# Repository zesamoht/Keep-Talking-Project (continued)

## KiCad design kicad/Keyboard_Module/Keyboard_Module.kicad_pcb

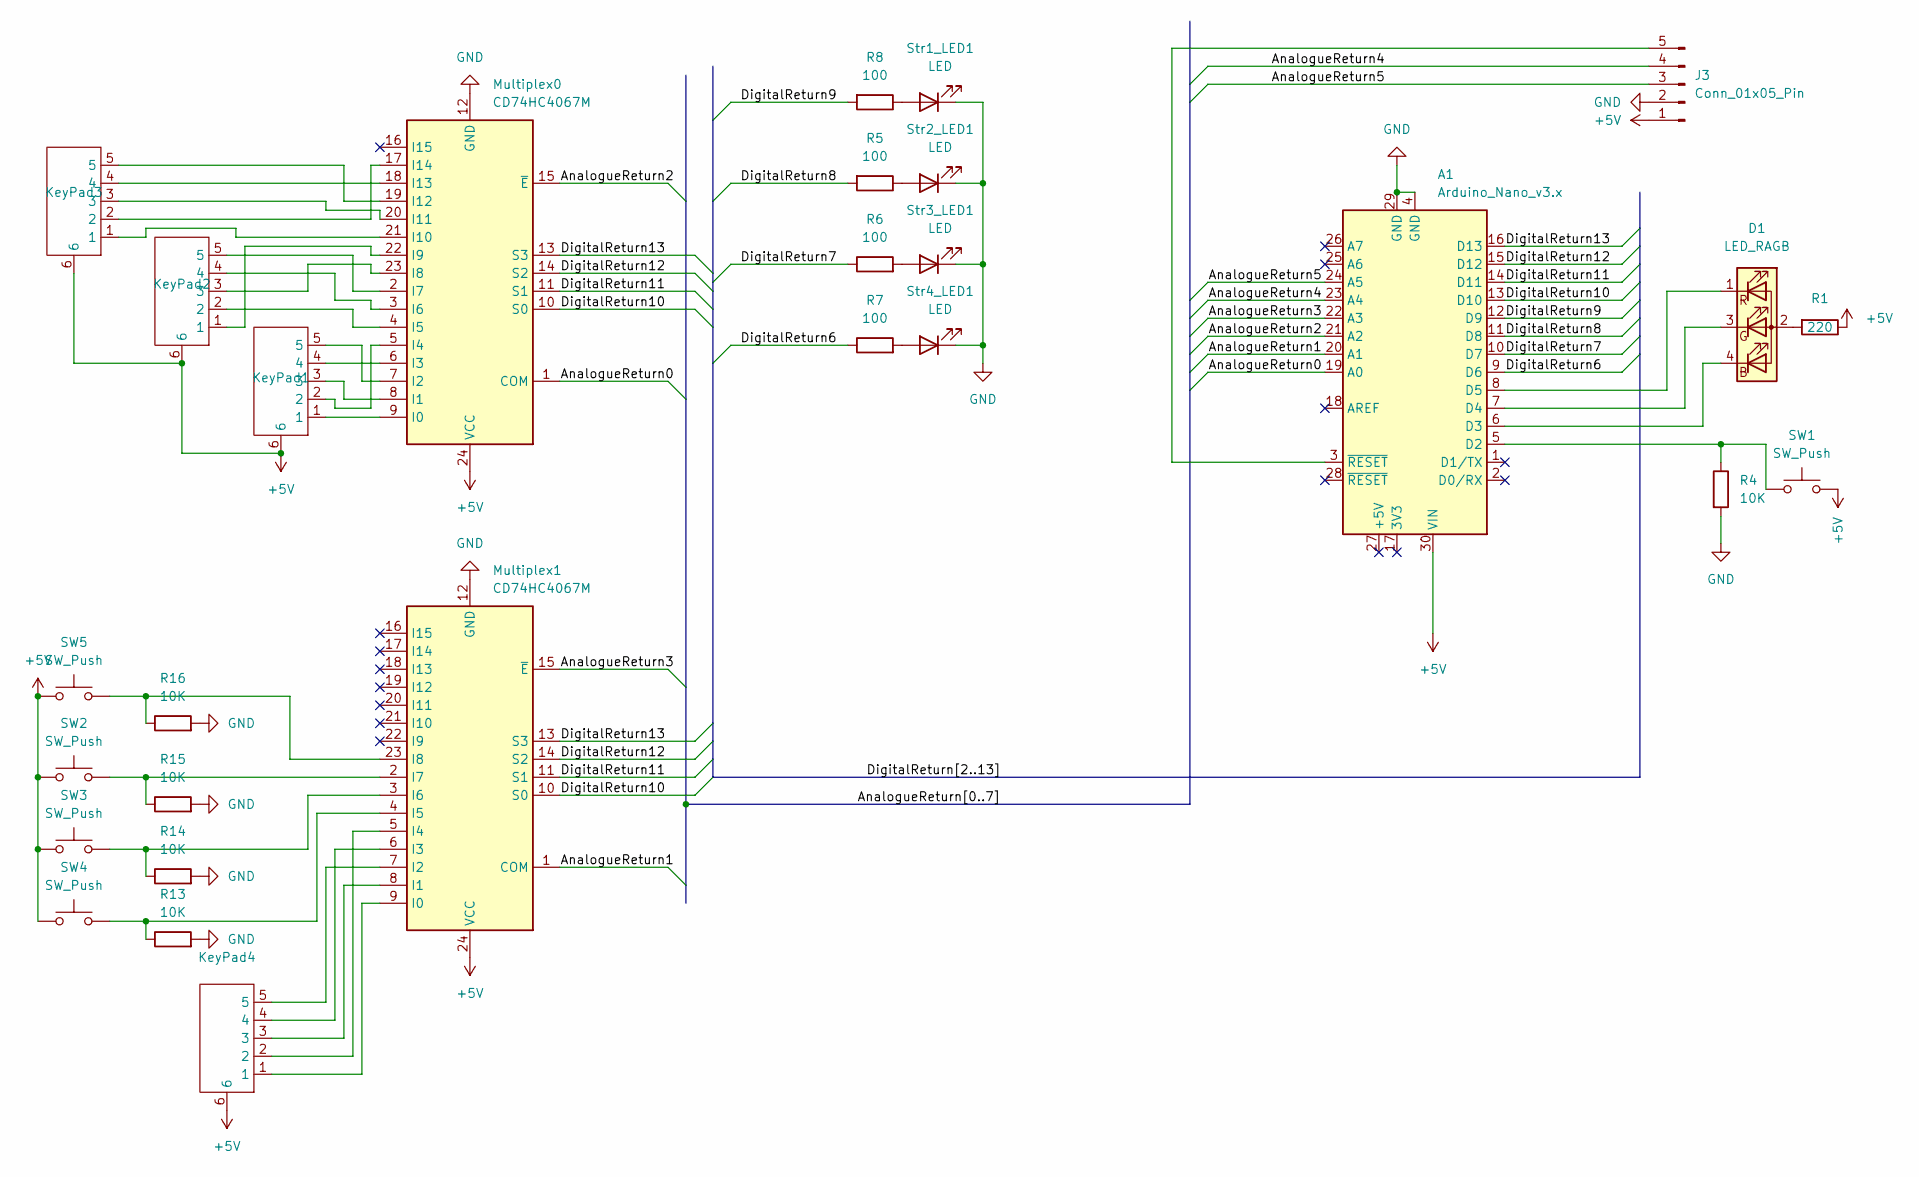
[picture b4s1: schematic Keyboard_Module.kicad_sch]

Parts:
A1: Arduino_Nano_v3.x; Arduino_Nano
D1: LED_RAGB; LED_D5.0mm-4_RGB_Staggered_Pins
J3: Conn_01x05_Pin; JST_XH_B5B-XH-A_1x05_P2.50mm_Vertical
KeyPad1, KeyPad2, KeyPad3, KeyPad4: Connector_PogoPin_6Pin
Multiplex0, Multiplex1: CD74HC4067M; CD74HC4067M Multiplexer Board
R1: 220; R_Axial_DIN0207_L6.3mm_D2.5mm_P7.62mm_Horizontal
R4, R13, R14, R15, R16: 10K; R_Axial_DIN0207_L6.3mm_D2.5mm_P7.62mm_Horizontal
R5, R6, R7, R8: 100; R_Axial_DIN0207_L6.3mm_D2.5mm_P7.62mm_Horizontal
SW1, SW2, SW3, SW4, SW5: SW_Push; SW_PUSH_6mm_H13mm
Str1_LED1, Str2_LED1, Str3_LED1, Str4_LED1: LED; LED_D5.0mm

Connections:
+5V: A1.30 (VIN), J3.1, KeyPad1.6, KeyPad2.6, KeyPad3.6, KeyPad4.6, Multiplex0.24 (VCC), Multiplex1.24 (VCC), R1.1, SW1.2, SW2.1, SW3.1, SW4.1, SW5.1
/AnalogueReturn0: A1.19 (A0), Multiplex0.1 (COM)
/AnalogueReturn1: A1.20 (A1), Multiplex1.1 (COM)
/AnalogueReturn2: A1.21 (A2), Multiplex0.15 (~E)
/AnalogueReturn3: A1.22 (A3), Multiplex1.15 (~E)
/AnalogueReturn4: A1.23 (A4), J3.4
/AnalogueReturn5: A1.24 (A5), J3.3
/DigitalReturn6: A1.9 (D6), R7.1
/DigitalReturn7: A1.10 (D7), R6.1
/DigitalReturn8: A1.11 (D8), R5.2
/DigitalReturn9: A1.12 (D9), R8.2
/DigitalReturn10: A1.13 (D10), Multiplex0.10 (S0), Multiplex1.10 (S0)
/DigitalReturn11: A1.14 (D11), Multiplex0.11 (S1), Multiplex1.11 (S1)
/DigitalReturn12: A1.15 (D12), Multiplex0.14 (S2), Multiplex1.14 (S2)
/DigitalReturn13: A1.16 (D13), Multiplex0.13 (S3), Multiplex1.13 (S3)
GND: A1.4 (GND), A1.29 (GND), J3.2, Multiplex0.12 (GND), Multiplex1.12 (GND), R4.2, R13.2, R14.2, R15.2, R16.2, Str1_LED1.1 (K), Str2_LED1.1 (K), Str3_LED1.1 (K), Str4_LED1.1 (K)
unnamed: A1.5 (D2), R4.1, SW1.1
unnamed: A1.6 (D3), D1.4 (BK)
unnamed: A1.7 (D4), D1.3 (GK)
unnamed: A1.8 (D5), D1.1 (RK)
unnamed: D1.2 (A), R1.2
unnamed: A1.3 (~RESET), J3.5
unnamed: KeyPad1.1, Multiplex0.9 (I0)
unnamed: KeyPad1.3, Multiplex0.8 (I1)
unnamed: KeyPad1.5, Multiplex0.7 (I2)
unnamed: KeyPad1.4, Multiplex0.6 (I3)
unnamed: KeyPad1.2, Multiplex0.5 (I4)
unnamed: KeyPad2.2, Multiplex0.4 (I5)
unnamed: KeyPad2.4, Multiplex0.3 (I6)
unnamed: KeyPad2.5, Multiplex0.2 (I7)
unnamed: KeyPad2.3, Multiplex0.23 (I8)
unnamed: KeyPad2.1, Multiplex0.22 (I9)
unnamed: KeyPad3.1, Multiplex0.21 (I10)
unnamed: KeyPad3.3, Multiplex0.20 (I11)
unnamed: KeyPad3.5, Multiplex0.19 (I12)
unnamed: KeyPad3.4, Multiplex0.18 (I13)
unnamed: KeyPad3.2, Multiplex0.17 (I14)
unnamed: KeyPad4.1, Multiplex1.9 (I0)
unnamed: KeyPad4.3, Multiplex1.8 (I1)
unnamed: KeyPad4.5, Multiplex1.7 (I2)
unnamed: KeyPad4.4, Multiplex1.6 (I3)
unnamed: KeyPad4.2, Multiplex1.5 (I4)
unnamed: Multiplex1.4 (I5), R13.1, SW4.2
unnamed: Multiplex1.3 (I6), R14.1, SW3.2
unnamed: Multiplex1.2 (I7), R15.1, SW2.2
unnamed: Multiplex1.23 (I8), R16.1, SW5.2
unnamed: R8.1, Str1_LED1.2 (A)
unnamed: R5.1, Str2_LED1.2 (A)
unnamed: R6.2, Str3_LED1.2 (A)
unnamed: R7.2, Str4_LED1.2 (A)

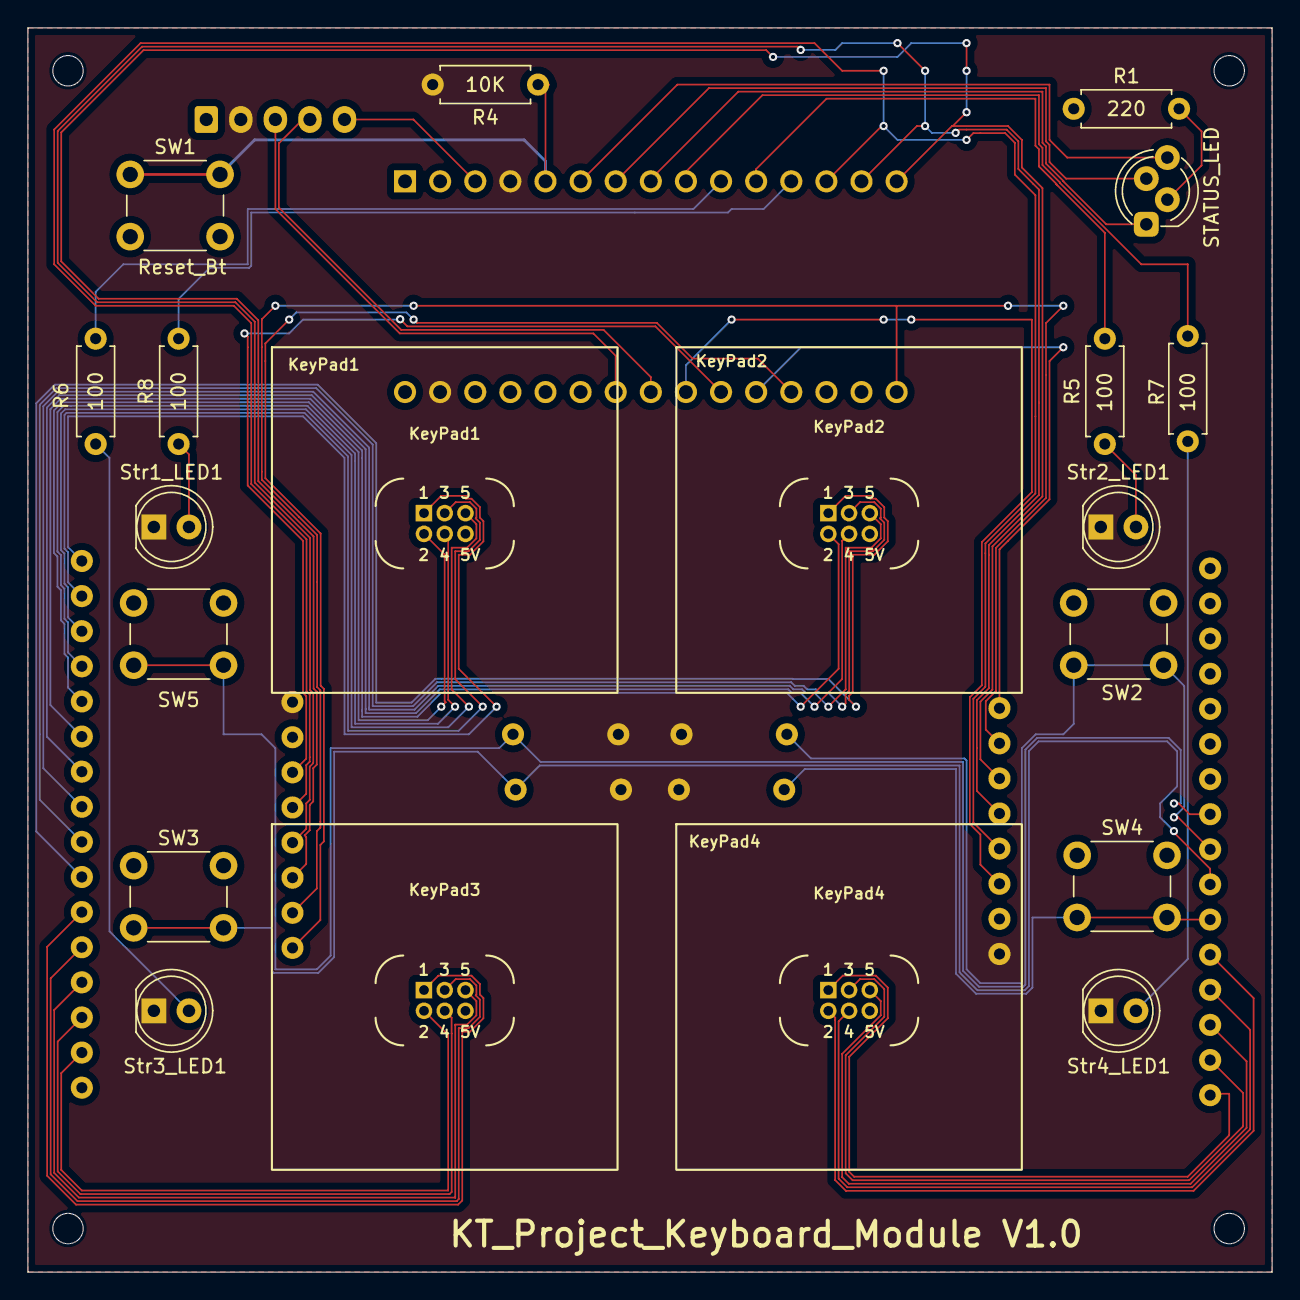
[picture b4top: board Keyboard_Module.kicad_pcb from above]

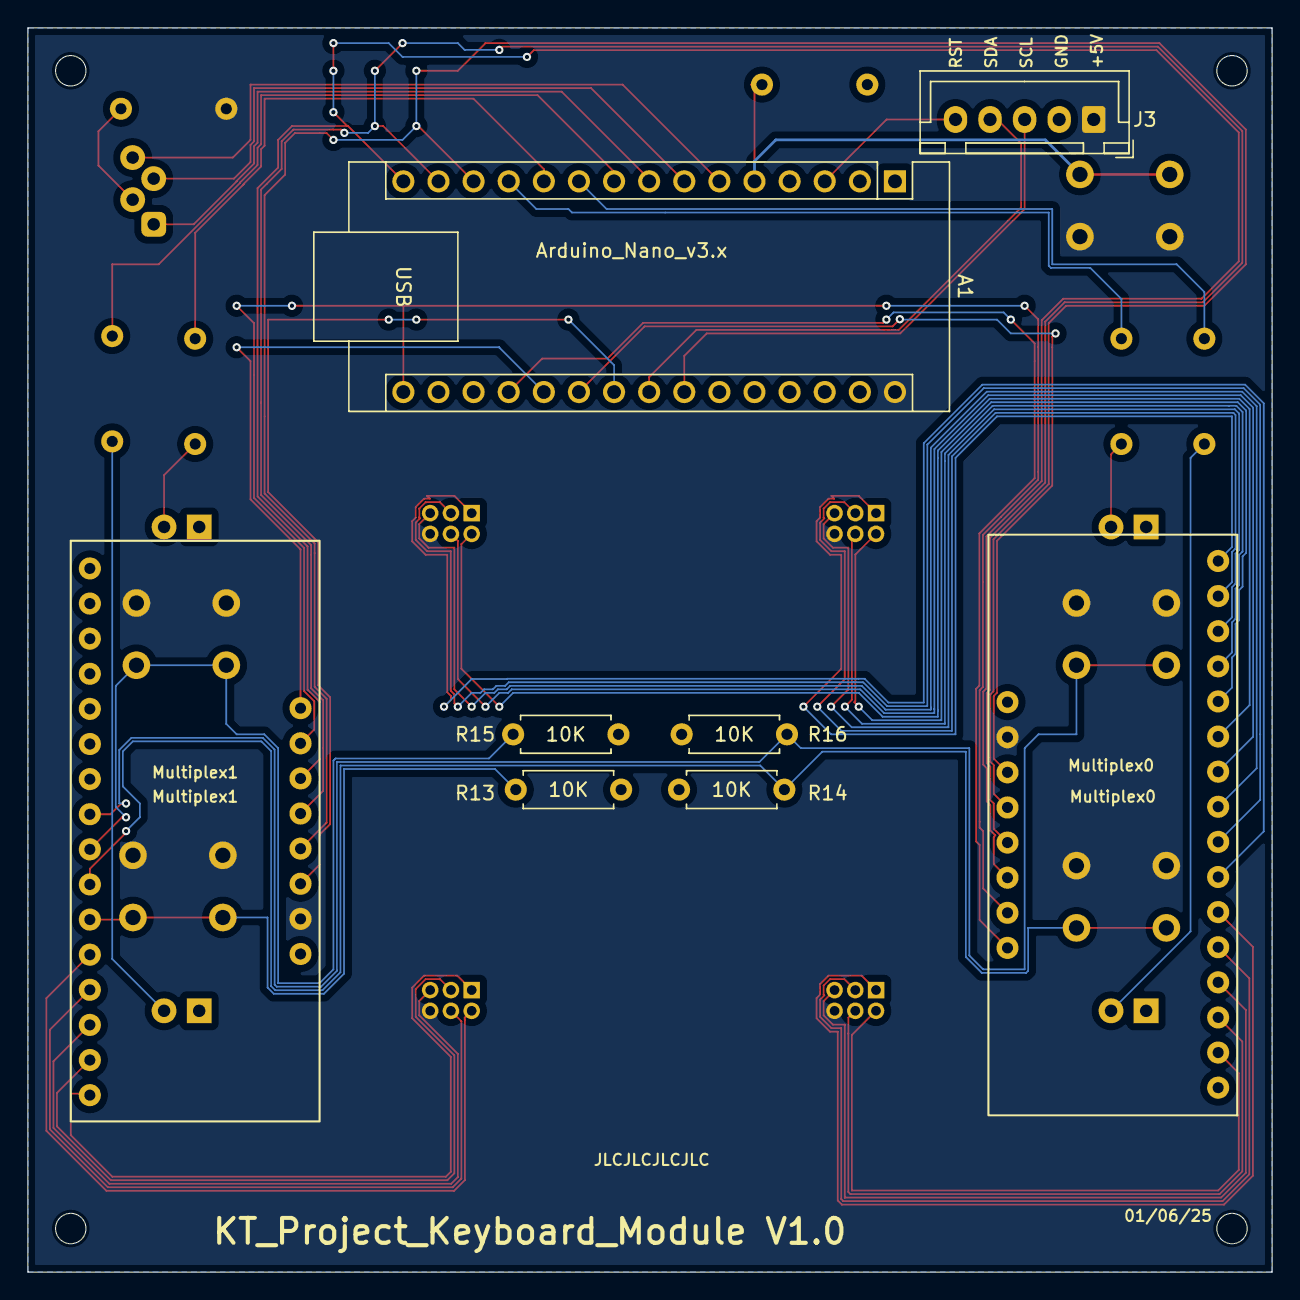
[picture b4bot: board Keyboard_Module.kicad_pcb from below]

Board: 2 copper layers, 90.0 x 90.0 mm, 28 parts (8 on the bottom side), 50 nets.

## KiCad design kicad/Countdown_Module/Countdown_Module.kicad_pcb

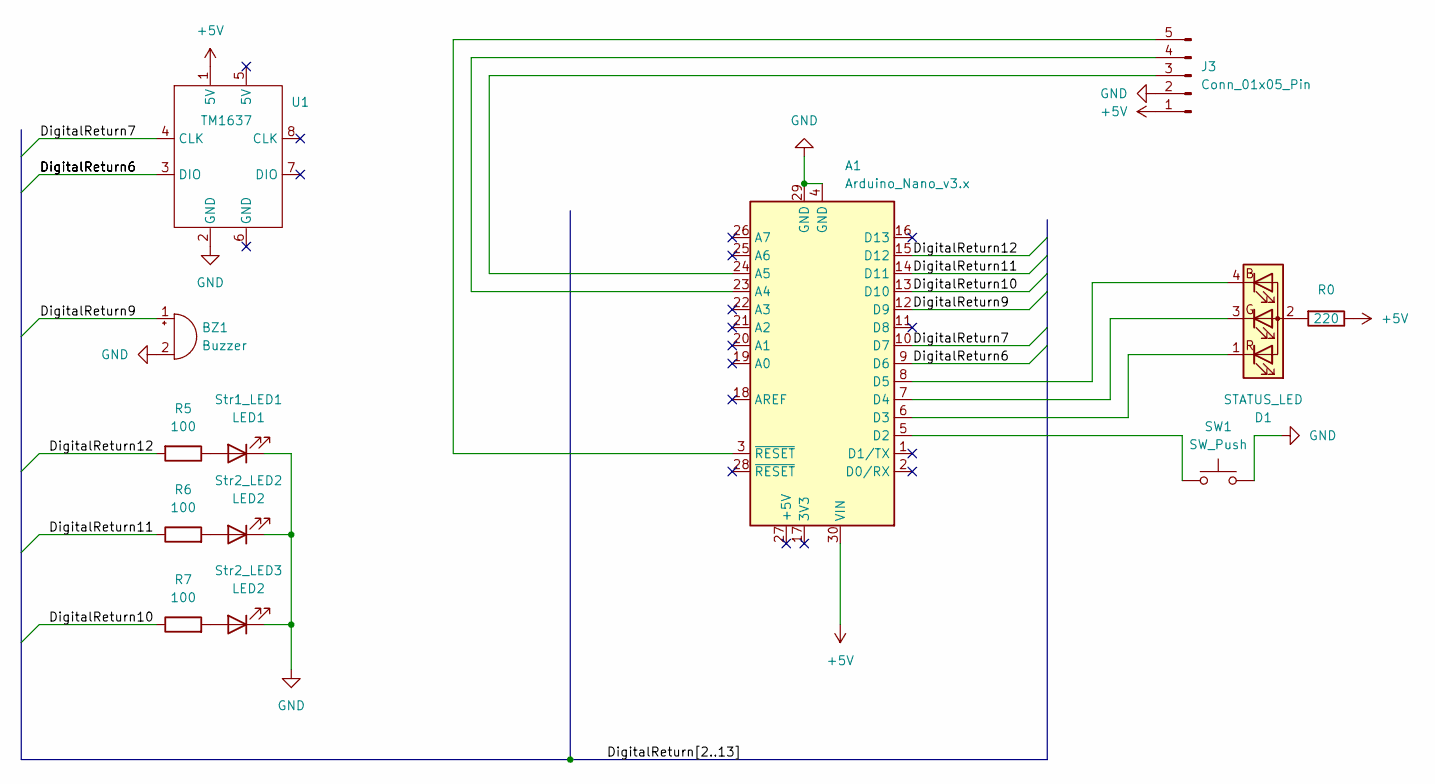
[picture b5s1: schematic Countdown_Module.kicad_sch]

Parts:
A1: Arduino_Nano_v3.x; Arduino_Nano
BZ1: Buzzer; Speaker_CUI_CMR-1206S-67
D1: STATUS_LED; LED_D5.0mm-4_RGB_Staggered_Pins
J3: Conn_01x05_Pin; JST_XH_B5B-XH-A_1x05_P2.50mm_Vertical
R0: 220; R_Axial_DIN0207_L6.3mm_D2.5mm_P7.62mm_Horizontal
R5, R6, R7: 100; R_Axial_DIN0207_L6.3mm_D2.5mm_P7.62mm_Horizontal
SW1: SW_Push; SW_PUSH_6mm_H13mm
Str1_LED1: LED1; LED_D5.0mm
Str2_LED2, Str2_LED3: LED2; LED_D5.0mm
U1: TM1637; TM1637_4Digits_7Segment_Display

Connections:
+5V: A1.30 (VIN), J3.1, R0.1, U1.1 (5V)
/DigitalReturn6: A1.9 (D6), U1.3 (DIO)
/DigitalReturn7: A1.10 (D7), U1.4 (CLK)
/DigitalReturn9: A1.12 (D9), BZ1.1 (+)
/DigitalReturn10: A1.13 (D10), R7.1
/DigitalReturn11: A1.14 (D11), R6.1
/DigitalReturn12: A1.15 (D12), R5.2
GND: A1.4 (GND), A1.29 (GND), BZ1.2 (-), J3.2, SW1.2, Str1_LED1.1 (K), Str2_LED2.1 (K), Str2_LED3.1 (K), U1.2 (GND)
unnamed: A1.23 (A4), J3.4
unnamed: A1.24 (A5), J3.3
unnamed: A1.5 (D2), SW1.1
unnamed: A1.6 (D3), D1.1 (RK)
unnamed: A1.7 (D4), D1.3 (GK)
unnamed: A1.8 (D5), D1.4 (BK)
unnamed: D1.2 (A), R0.2
unnamed: A1.3 (~RESET), J3.5
unnamed: R5.1, Str1_LED1.2 (A)
unnamed: R6.2, Str2_LED2.2 (A)
unnamed: R7.2, Str2_LED3.2 (A)

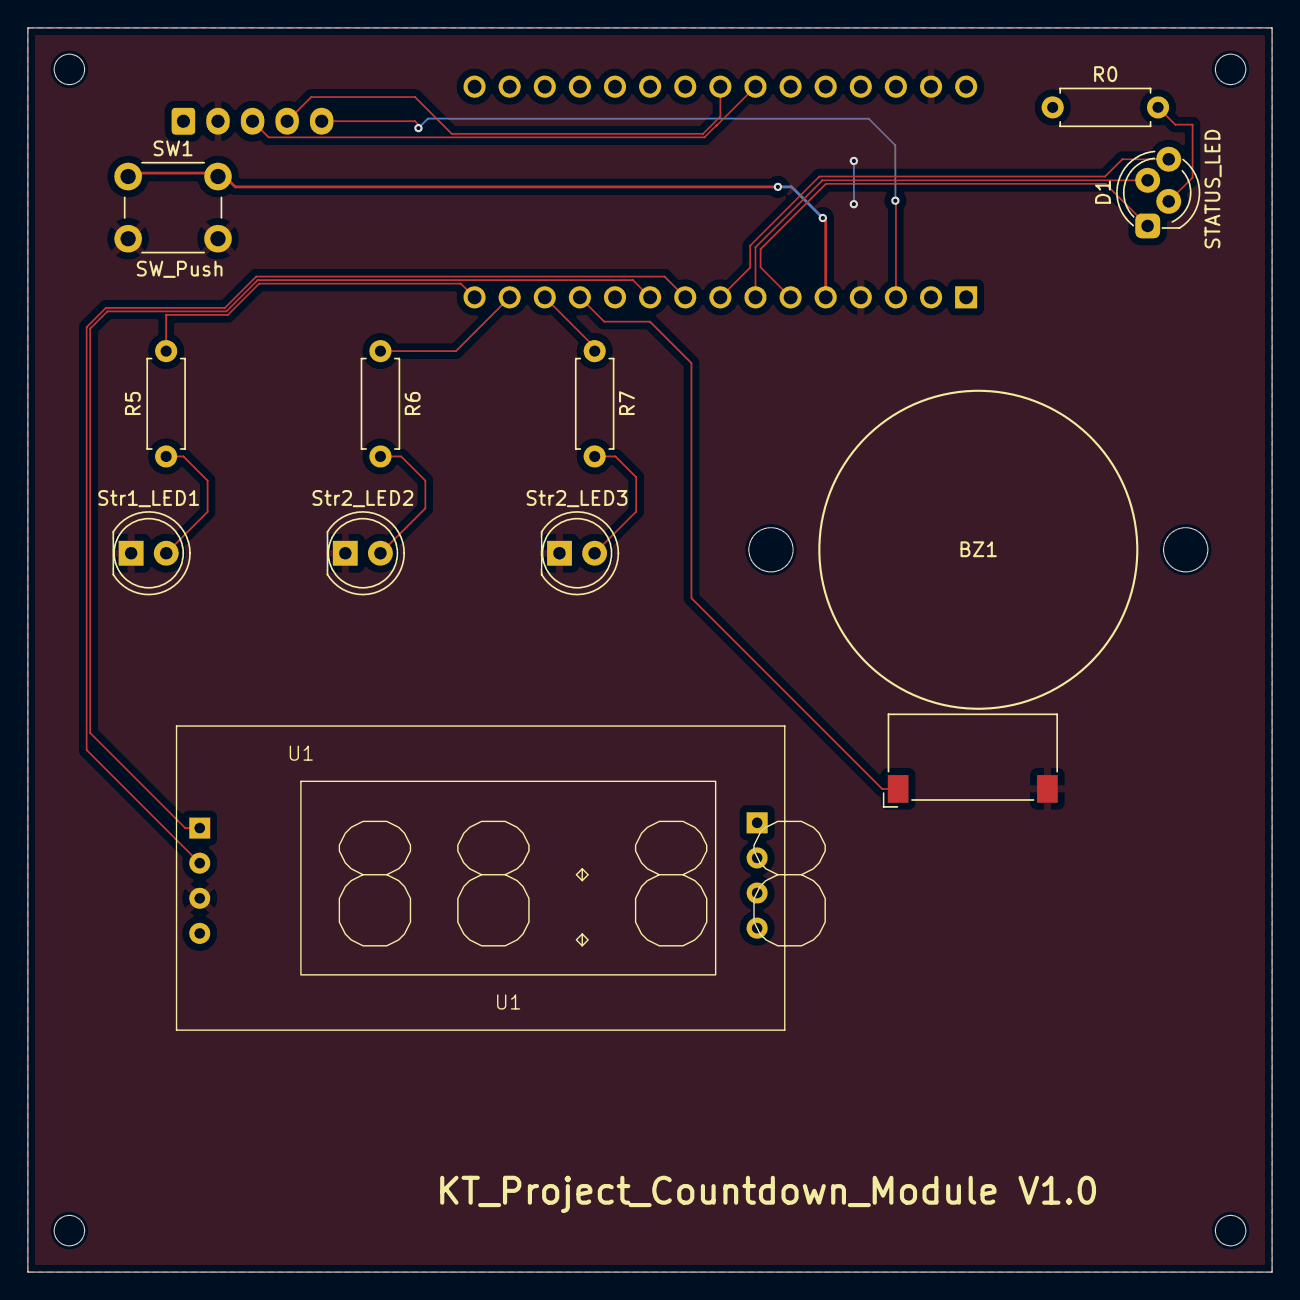
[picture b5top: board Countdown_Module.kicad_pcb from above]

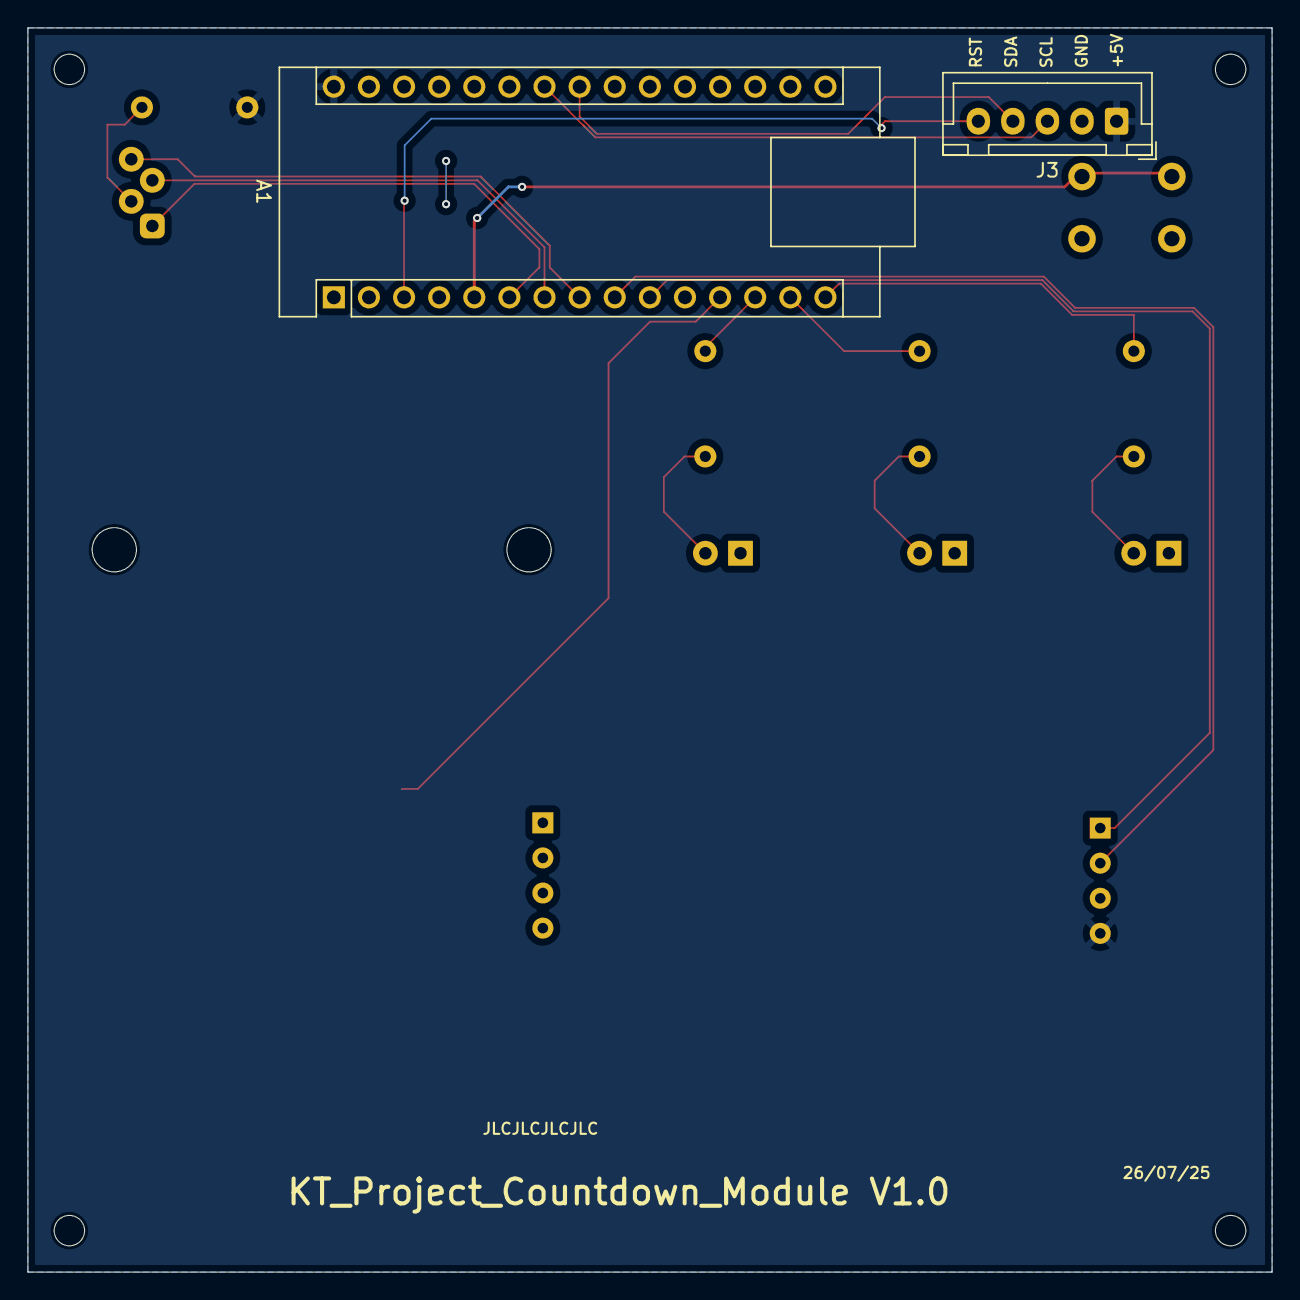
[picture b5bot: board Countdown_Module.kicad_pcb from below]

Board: 2 copper layers, 90.0 x 90.0 mm, 13 parts (2 on the bottom side), 19 nets.

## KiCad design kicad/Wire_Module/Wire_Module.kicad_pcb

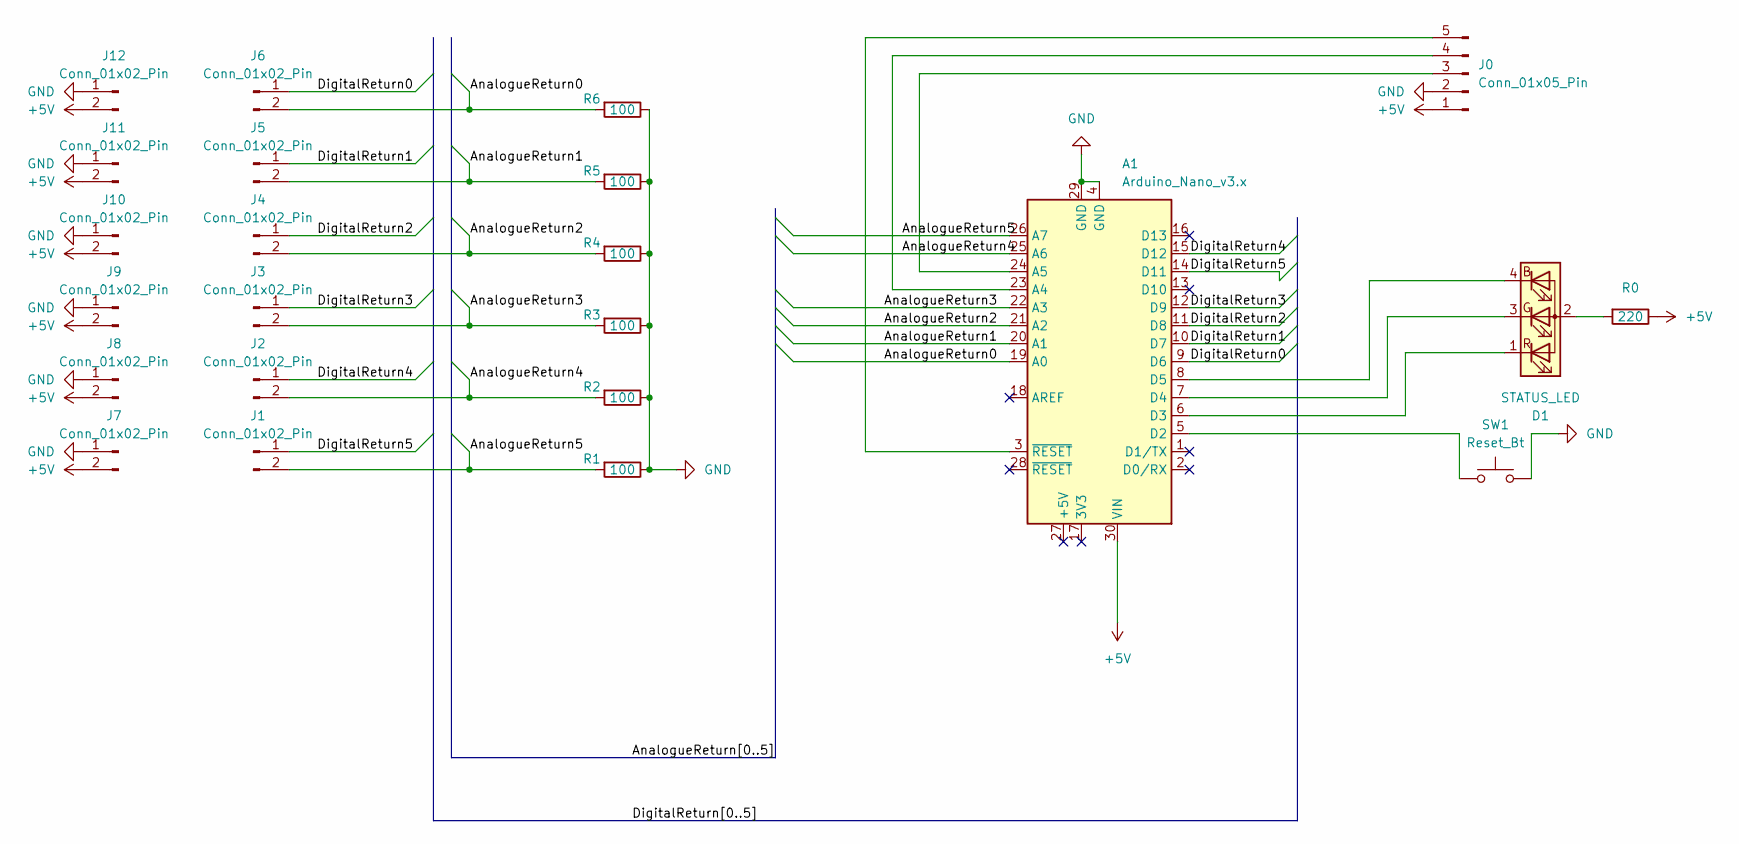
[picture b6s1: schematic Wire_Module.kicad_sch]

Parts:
A1: Arduino_Nano_v3.x; Arduino_Nano
D1: STATUS_LED; LED_D5.0mm-4_RGB_Staggered_Pins
J0: Conn_01x05_Pin; JST_XH_B5B-XH-A_1x05_P2.50mm_Vertical
J1, J2, J3, J4, J5, J6, J7, J8, J9, J10, J11, J12: Conn_01x02_Pin; JST_XH_B2B-XH-A_1x02_P2.50mm_Vertical
R0: 220; R_Axial_DIN0207_L6.3mm_D2.5mm_P7.62mm_Horizontal
R1, R2, R3, R4, R5, R6: 100; R_Axial_DIN0207_L6.3mm_D2.5mm_P7.62mm_Horizontal
SW1: Reset_Bt; SW_PUSH_6mm_H13mm

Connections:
+5V: A1.30 (VIN), J0.1, J7.2, J8.2, J9.2, J10.2, J11.2, J12.2, R0.1
/AnalogueReturn0: A1.19 (A0), J6.2, R6.2
/AnalogueReturn1: A1.20 (A1), J5.2, R5.2
/AnalogueReturn2: A1.21 (A2), J4.2, R4.2
/AnalogueReturn3: A1.22 (A3), J3.2, R3.2
/AnalogueReturn4: A1.25 (A6), J2.2, R2.2
/AnalogueReturn5: A1.26 (A7), J1.2, R1.2
/DigitalReturn0: A1.9 (D6), J6.1
/DigitalReturn1: A1.10 (D7), J5.1
/DigitalReturn2: A1.11 (D8), J4.1
/DigitalReturn3: A1.12 (D9), J3.1
/DigitalReturn4: A1.15 (D12), J2.1
/DigitalReturn5: A1.14 (D11), J1.1
GND: A1.4 (GND), A1.29 (GND), J0.2, J7.1, J8.1, J9.1, J10.1, J11.1, J12.1, R1.1, R2.1, R3.1, R4.1, R5.1, R6.1, SW1.2
unnamed: A1.23 (A4), J0.4
unnamed: A1.24 (A5), J0.3
unnamed: A1.5 (D2), SW1.1
unnamed: A1.6 (D3), D1.1 (RK)
unnamed: A1.7 (D4), D1.3 (GK)
unnamed: A1.8 (D5), D1.4 (BK)
unnamed: D1.2 (A), R0.2
unnamed: A1.3 (~RESET), J0.5

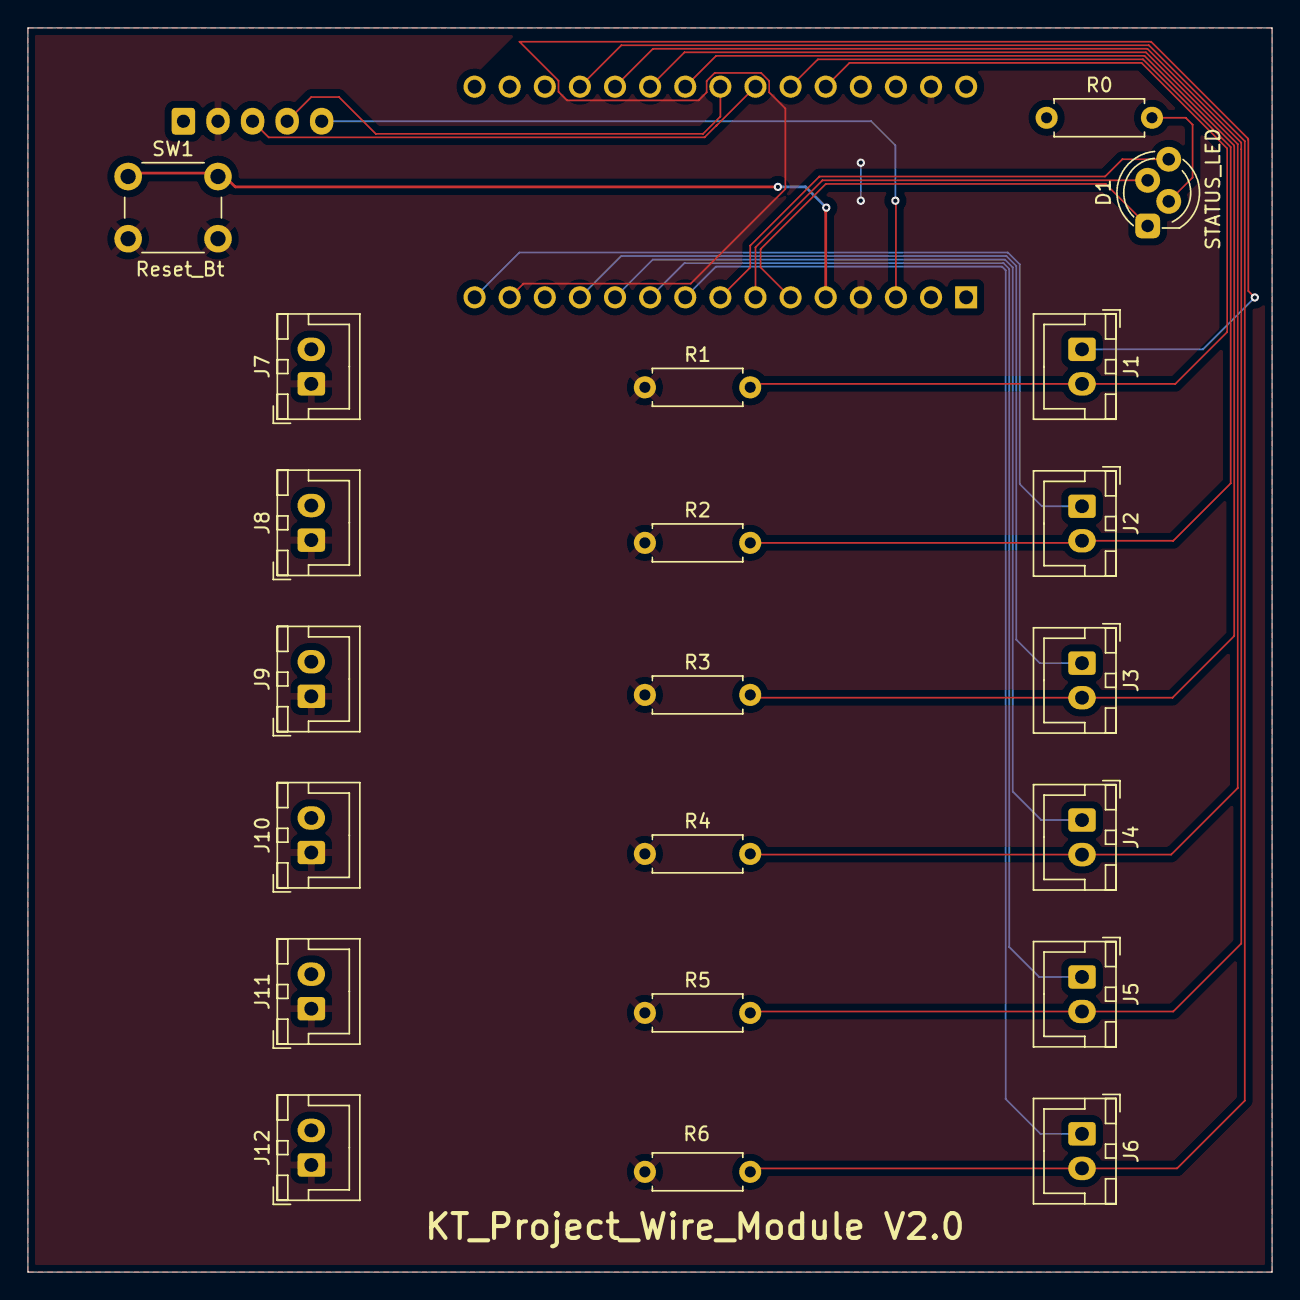
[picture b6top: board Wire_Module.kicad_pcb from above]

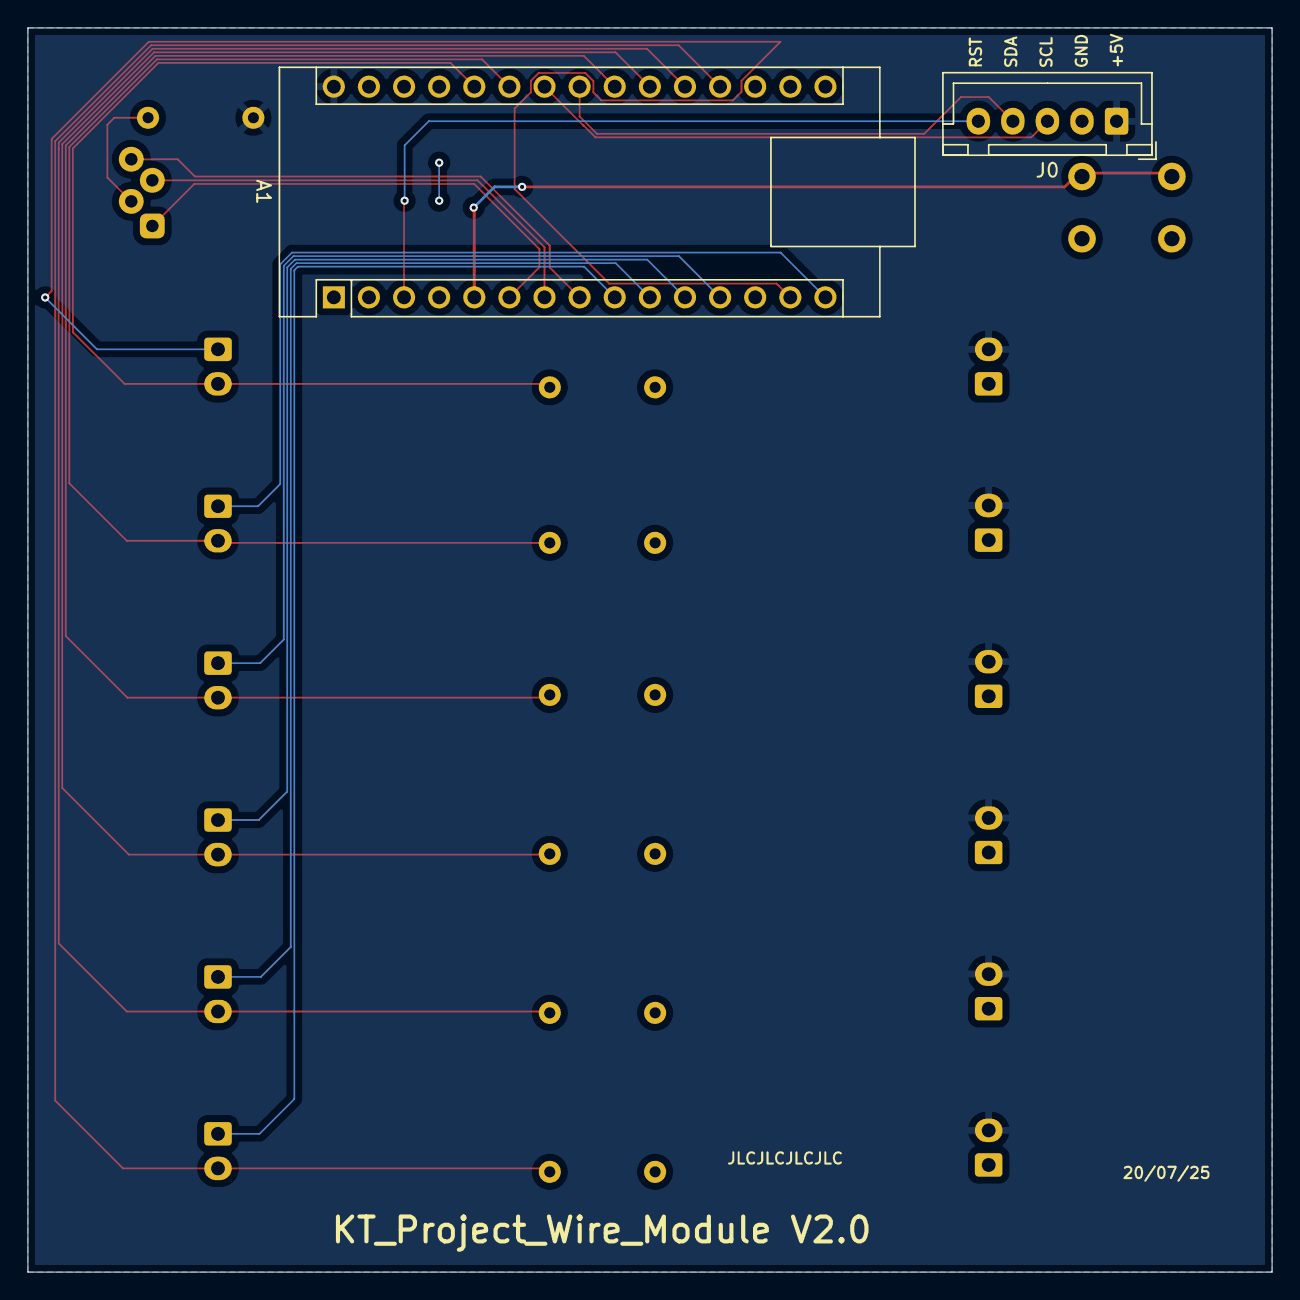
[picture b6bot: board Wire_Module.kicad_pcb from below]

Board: 2 copper layers, 90.0 x 90.0 mm, 23 parts (2 on the bottom side), 22 nets.

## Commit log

2026-04-25 Create .gitignore for Kicad useless files
2026-04-25 Update .gitignore V2
2026-04-25 Create README.md
    For all the arduino code module per module
2026-04-25 Create README.md
    For the Kkicad folder
2026-04-25 Kicad for Button Module
2026-04-25 Wire module Kickad upload
2026-04-25 Countdown module Kickad
2026-04-25 Maze_Module Kicad
2026-04-25 Keyboard_Module
2026-04-25 Upload all Kicad
2026-04-25 Upload all Arduino code
2026-06-06 refactor hold button logic
2026-06-07 Fix keyboard join state and live button scanning
2026-06-07 Align keyboard comments with project style
2026-06-07 Preserve mainline comments in keyboard fix
2026-06-07 Decode keyboard keys using PCB channel order
2026-06-07 Update KT_Module_Keyboard.ino
    Change button array order to match physical pinout
2026-06-10 Add PlatformIO environments for Arduino modules
2026-06-10 Ignore PlatformIO generated files
2026-06-11 Add KeepTalkingCore library manifest
2026-06-11 Add shared Keep Talking protocol constants
2026-06-11 Add shared status LED helper
2026-06-11 Implement shared status LED helper
2026-06-11 Add base Keep Talking module class
2026-06-11 Implement base Keep Talking module class
2026-06-11 Document KeepTalkingCore migration approach
2026-06-11 Refactor Simon Says module to use KeepTalkingCore
